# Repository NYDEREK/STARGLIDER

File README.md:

<h1>STARGLIDER MainBoard rev1 - Datasheet</h1>

<h2>Main Board Features</h2>

<ul>
  <li>STM32G474RET6 microcontroller in LQFP64 package</li>
  <li>RGB LED diode</li>
  <li>JST SH SM0XB SSR TB connectors</li>
  <li>MIPI10 - STDC14 programmer connector</li>
  <li>Tag connector programmer footprint</li>
  <li>Micro SD card slot</li>
  <li>Buzzer</li>
  <li>BME280 Temperature, Humidity &amp; Pressure sensor</li>
  <li>LSM6DS3 Accelerometer &amp; Gyroscope IMU module</li>
  <li>USB 2.0 connector</li>
</ul>

<h2>Description</h2>
<p>
Main Board is the most important PCB in the STARGLIDER build.  
It controls all other modules, saves data on the micro-SD card, calculates flight data 
such as attitude, roll, pitch, and yaw, and measures Temperature, Humidity, and Pressure.  
Thanks to the built-in “Cordic” it is able to easily calculate flight path &amp; Kalman filter.
</p>

<h2>Main Board Pinout</h2>

<p>
The Main Board provides 6 different connectors for GPIO, ADC, PWM, Communication, and one connector for Power.  
Input voltage range: <strong>5 – 9 V</strong>.  
Current consumption without external peripherals: <strong>&lt; 1A</strong>.  
Logic pin voltage should not exceed <strong>3.3V</strong>.  
</p>
<p>
Board capabilities include Low-power UART to LSM6DS3 IMU (U7).  
More information is available in the schematic provided in the project files.
</p>

<h2>Programming</h2>

<p>Main Board can be programmed by ST-Link from STMicroelectronics.</p>
<p>Supported development toolchains:</p>
<ul>
  <li>IAR Systems® – IAR Embedded Workbench®</li>
  <li>Keil® – MDK-ARM</li>
  <li>STMicroelectronics – STM32CubeIDE</li>
</ul>

<h2>Measurements</h2>
<p>Main Board is able to measure:</p>
<ul>
  <li>Accelerations</li>
  <li>Angular velocity</li>
  <li>Temperature</li>
  <li>Humidity</li>
  <li>Pressure</li>
  <li>Voltage</li>
</ul>

<h2>LSM6DS3</h2>

<p>
The LSM6DS3TR-C is a system-in-package featuring a 3D digital accelerometer and a 3D digital gyroscope.  
It performs at 0.90 mA in high-performance mode and enables always-on low-power features.  
</p>
<p>
Acceleration range: ±2/±4/±8/±16 g<br>
Angular rate range: ±125/±250/±500/±1000/±2000 dps
</p>

<h2>BME280</h2>

<p>
The BME280 is a combined digital humidity, pressure, and temperature sensor.  
It provides fast response time, high accuracy over a wide temperature range, and optimized low-noise temperature sensing.  
</p>
<p>
Pressure sensor: absolute barometric, high accuracy, lower noise than BMP180.<br>
Temperature output: used for compensation of pressure &amp; humidity, also for ambient temperature estimation.
</p>

<h2>Analog to Digital Converter (ADC)</h2>
<p>The STM32G474RET6 includes 5 successive approximation ADCs with:</p>
<ul>
  <li>12-bit native resolution, built-in calibration</li>
  <li>Up to 4 Msps conversion rate (25 ns sampling time)</li>
  <li>Up to 6.66 Msps at 6-bit resolution</li>
</ul>
<p>
The MCU performance allows the Main Board to measure voltages in the 0 – 3.3 V range with high resolution and speed.
</p>

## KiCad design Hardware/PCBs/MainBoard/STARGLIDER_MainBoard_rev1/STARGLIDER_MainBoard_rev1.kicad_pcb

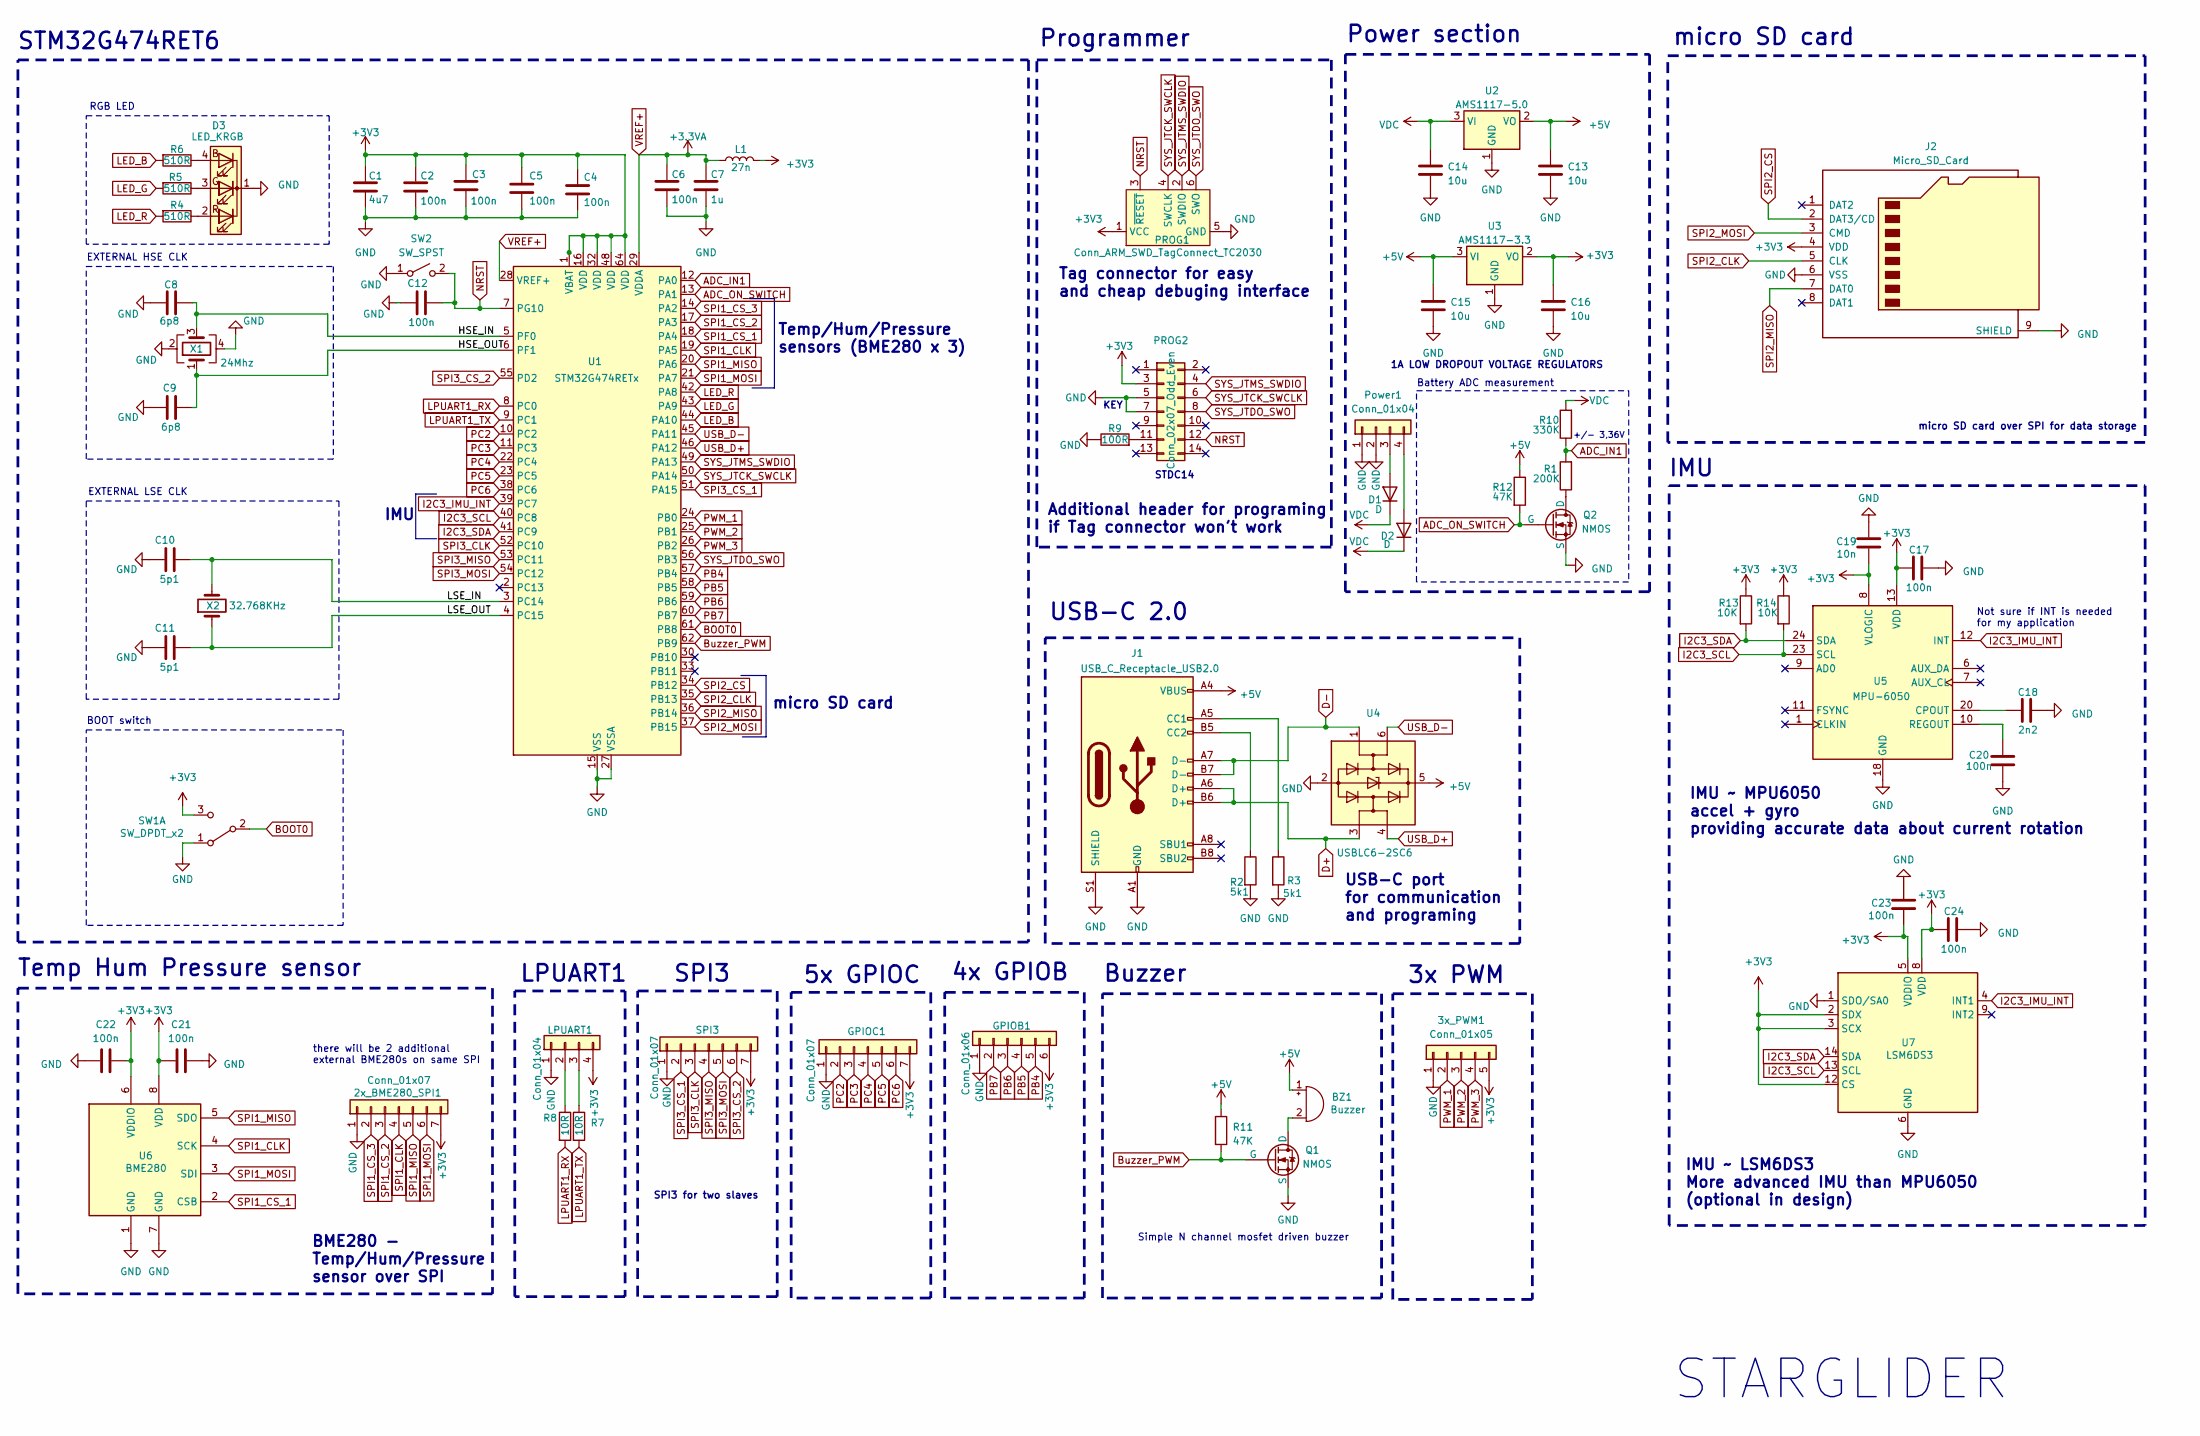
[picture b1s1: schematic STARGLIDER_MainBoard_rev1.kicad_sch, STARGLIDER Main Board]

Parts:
2x_BME280_SPI1: Conn_01x07; JST_SH_SM07B-SRSS-TB_1x07-1MP_P1.00mm_Horizontal
3x_PWM1: Conn_01x05; JST_SH_SM05B-SRSS-TB_1x05-1MP_P1.00mm_Horizontal
BZ1: Buzzer; MagneticBuzzer_PUI_AT-0927-TT-6-R
C1: 4u7; C_0603_1608Metric
C2, C3, C4, C5, C6, C12, C17, C20, C21, C22, C23, C24: 100n; C_0603_1608Metric
C7: 1u; C_0603_1608Metric
C8, C9: 6p8; C_0603_1608Metric
C10, C11: 5p1; C_0603_1608Metric
C13, C14, C15, C16: 10u; C_0603_1608Metric
C18: 2n2; C_0603_1608Metric
C19: 10n; C_0603_1608Metric
D1, D2: D; D_SOD-123
D3: LED_KRGB; LED_RGB_5050-6; Part number TC5050RGBF08-3CJH-AF53A
GPIOB1: Conn_01x06; JST_SH_SM06B-SRSS-TB_1x06-1MP_P1.00mm_Horizontal
GPIOC1: Conn_01x07; JST_SH_SM07B-SRSS-TB_1x07-1MP_P1.00mm_Horizontal
J1: USB_C_Receptacle_USB2.0; USB_C_Receptacle_GCT_USB4105-xx-A_16P_TopMnt_Horizontal
J2: Micro_SD_Card; micro_SD_card
L1: 27n; L_0603_1608Metric
LPUART1: Conn_01x04; JST_SH_SM04B-SRSS-TB_1x04-1MP_P1.00mm_Horizontal
PROG1: Conn_ARM_SWD_TagConnect_TC2030; Tag-Connect_TC2030-IDC-FP_2x03_P1.27mm_Vertical
PROG2: Conn_02x07_Odd_Even; PinHeader_2x07_P1.27mm_Vertical_SMD
Power1: Conn_01x04; JST_SH_SM04B-SRSS-TB_1x04-1MP_P1.00mm_Horizontal
Q1, Q2: NMOS; PUOLOP 2N7002-SOT23
R1: 200K; R_0603_1608Metric
R2, R3: 5k1; R_0603_1608Metric
R4, R5, R6: 510R; R_0603_1608Metric
R7, R8: 10R; R_0603_1608Metric
R9: 100R; R_0603_1608Metric
R10: 330K; R_0603_1608Metric
R11, R12: 47K; R_0603_1608Metric
R13, R14: 10K; R_0603_1608Metric
SPI3: Conn_01x07; JST_SH_SM07B-SRSS-TB_1x07-1MP_P1.00mm_Horizontal
SW1: SW_DPDT_x2; SW_SPDT_PCM12
SW2: SW_SPST; SW_SPST_CK_RS282G05A3
U1: STM32G474RETx; LQFP-64_10x10mm_P0.5mm
U2: AMS1117-5.0; SOT-223-3_TabPin2
U3: AMS1117-3.3; SOT-223-3_TabPin2
U4: USBLC6-2SC6; SOT-23-6
U5: MPU-6050; InvenSense_QFN-24_4x4mm_P0.5mm
U6: BME280; Bosch_LGA-8_2.5x2.5mm_P0.65mm_ClockwisePinNumbering
U7: LSM6DS3; LGA-14_3x2.5mm_P0.5mm_LayoutBorder3x4y
X1: 24Mhz; Crystal_SMD_2016-4Pin_2.0x1.6mm
X2: 32.768KHz; Crystal_SMD_3215-2Pin_3.2x1.5mm

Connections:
+3V3: 2x_BME280_SPI1.7, 3x_PWM1.5, C1.1, C2.1, C3.1, C4.1, C5.1, C16.1, C17.2, C19.1, C21.1, C22.2, C23.1, C24.2, GPIOB1.6, GPIOC1.7, J2.4 (VDD), L1.2, LPUART1.4, PROG1.1 (VCC), PROG2.3, R13.1, R14.1, SPI3.7, SW1.3 (C), U1.1 (VBAT), U1.16 (VDD), U1.32 (VDD), U1.48 (VDD), U1.64 (VDD), U3.2 (VO), U5.8 (VLOGIC), U5.13 (VDD), U6.6 (VDDIO), U6.8 (VDD), U7.2 (SDX), U7.3 (SCX), U7.5 (VDDIO), U7.8 (VDD), U7.12 (CS); also elsewhere on the board
+5V: BZ1.1 (-), C13.1, C15.1, J1.A4 (VBUS), J1.A9 (VBUS), J1.B4 (VBUS), J1.B9 (VBUS), R11.1, R12.1, U2.2 (VO), U3.3 (VI), U4.5 (VBUS)
/HSE_IN: C8.2, U1.5 (PF0), X1.3
/HSE_OUT: C9.2, U1.6 (PF1), X1.1
/LSE_IN: C10.2, U1.3 (PC14), X2.2
/LSE_OUT: C11.2, U1.4 (PC15), X2.1
ADC_IN1: R1.2, R10.1, U1.12 (PA0)
ADC_ON_SWITCH: Q2.2 (G), R12.2, U1.13 (PA1)
BOOT0: SW1.2 (B), U1.61 (PB8); also elsewhere on the board
Buzzer_PWM: Q1.2 (G), R11.2, U1.62 (PB9)
D+: J1.A6 (D+), J1.B6 (D+), U4.3 (I/O2)
D-: J1.A7 (D-), J1.B7 (D-), U4.1 (I/O1)
GND: 2x_BME280_SPI1.1, 3x_PWM1.1, C1.2, C2.2, C3.2, C4.2, C5.2, C6.2, C7.2, C8.1, C9.1, C10.1, C11.1, C12.1, C13.2, C14.2, C15.2, C16.2, C17.1, C18.1, C19.2, C20.2, C21.2, C22.1, C23.2, C24.1, D3.1 (K), GPIOB1.1, GPIOC1.1, J1.A1 (GND), J1.A12 (GND), J1.B1 (GND), J1.B12 (GND), J1.S1 (SHIELD), J2.6 (VSS), J2.9 (SHIELD), LPUART1.1, PROG1.5 (GND), PROG2.5, PROG2.7, Power1.1, Power1.2, Q1.3 (S), Q2.3 (S), R2.2, R3.2, R9.1, SPI3.1, SW1.1 (A), SW2.1 (A), U1.15 (VSS), U1.27 (VSSA), U1.31 (VSS), U1.47 (VSS), U1.63 (VSS), U2.1 (GND), U3.1 (GND), U4.2 (GND), U5.18 (GND), U6.1 (GND), U6.7 (GND), U7.1 (SDO/SA0), U7.6 (GND), U7.7 (GND), X1.2, X1.4; also elsewhere on the board
I2C3_IMU_INT: U1.39 (PC7), U5.12 (INT), U7.4 (INT1)
I2C3_SCL: R14.2, U1.40 (PC8), U5.23 (SCL), U7.13 (SCL)
I2C3_SDA: R13.2, U1.41 (PC9), U5.24 (SDA), U7.14 (SDA)
LED_B: R6.2, U1.44 (PA10)
LED_G: R5.2, U1.43 (PA9)
LED_R: R4.2, U1.42 (PA8)
LPUART1_RX: R8.2, U1.8 (PC0)
LPUART1_TX: R7.2, U1.9 (PC1)
NRST: C12.2, PROG1.3 (~RESET), PROG2.12, SW2.2 (B), U1.7 (PG10); also elsewhere on the board
unnamed: BZ1.2 (+), Q1.1 (D)
unnamed: D1.2 (A), Power1.3
unnamed: D2.2 (A), Power1.4
unnamed: D3.4 (BA), R6.1
unnamed: D3.3 (GA), R5.1
unnamed: D3.2 (RA), R4.1
unnamed: J1.A5 (CC1), R3.1
unnamed: J1.B5 (CC2), R2.1
unnamed: LPUART1.2, R8.1
unnamed: LPUART1.3, R7.1
unnamed 32: PROG2.11, R9.2; also elsewhere on the board
unnamed: Q2.1 (D), R1.1
unnamed: C18.2, U5.20 (CPOUT)
unnamed: C20.1, U5.10 (REGOUT)
PB4: GPIOB1.5, U1.57 (PB4)
PB5: GPIOB1.4, U1.58 (PB5)
PB6: GPIOB1.3, U1.59 (PB6)
PB7: GPIOB1.2, U1.60 (PB7)
PC2: GPIOC1.2, U1.10 (PC2)
PC3: GPIOC1.3, U1.11 (PC3)
PC4: GPIOC1.4, U1.22 (PC4)
PC5: GPIOC1.5, U1.23 (PC5)
PC6: GPIOC1.6, U1.38 (PC6)
PWM_1: 3x_PWM1.2, U1.24 (PB0)
PWM_2: 3x_PWM1.3, U1.25 (PB1)
PWM_3: 3x_PWM1.4, U1.26 (PB2)
SPI1_CLK: 2x_BME280_SPI1.4, U1.19 (PA5), U6.4 (SCK)
SPI1_CS_1: U1.18 (PA4), U6.2 (CSB)
SPI1_CS_2: 2x_BME280_SPI1.3, U1.17 (PA3)
SPI1_CS_3: 2x_BME280_SPI1.2, U1.14 (PA2)
SPI1_MISO: 2x_BME280_SPI1.5, U1.20 (PA6), U6.5 (SDO)
SPI1_MOSI: 2x_BME280_SPI1.6, U1.21 (PA7), U6.3 (SDI)
SPI2_CLK: J2.5 (CLK), U1.35 (PB13)
SPI2_CS: J2.2 (DAT3/CD), U1.34 (PB12)
SPI2_MISO: J2.7 (DAT0), U1.36 (PB14)
SPI2_MOSI: J2.3 (CMD), U1.37 (PB15)
SPI3_CLK: SPI3.3, U1.52 (PC10)
SPI3_CS_1: SPI3.2, U1.51 (PA15)
SPI3_CS_2: SPI3.6, U1.55 (PD2)
SPI3_MISO: SPI3.4, U1.53 (PC11)
SPI3_MOSI: SPI3.5, U1.54 (PC12)
SYS_JTCK_SWCLK: PROG1.4 (SWCLK), PROG2.6, U1.50 (PA14); also elsewhere on the board
SYS_JTDO_SWO: PROG1.6 (SWO), PROG2.8, U1.56 (PB3); also elsewhere on the board
SYS_JTMS_SWDIO: PROG1.2 (SWDIO), PROG2.4, U1.49 (PA13); also elsewhere on the board
USB_D+: U1.46 (PA12), U4.4 (I/O2)
USB_D-: U1.45 (PA11), U4.6 (I/O1)
VDC: C14.1, D1.1 (K), D2.1 (K), R10.2, U2.3 (VI)
VREF+: C6.1, C7.1, L1.1, U1.28 (VREF+), U1.29 (VDDA)

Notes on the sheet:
BME280 - Temp/Hum/Pressure sensor over SPI
KEY
Programmer
IMU
STM32G474RET6
micro SD card
USB-C 2.0
SPI3 for two slaves
3x PWM
Tag connector for easy and cheap debuging interface
Additional header for programing if Tag connector won't work
IMU ~ MPU6050 accel + gyro providing accurate data about current rotation
Not sure if INT is needed for my application
SPI3
LPUART1
micro SD card over SPI for data storage
+/- 3,36V
BOOT switch
STARGLIDER
4x GPIOB
EXTERNAL HSE CLK
RGB LED
there will be 2 additional external BME280s on same SPI
IMU ~ LSM6DS3 More advanced IMU than MPU6050 (optional in design)
Simple N channel mosfet driven buzzer
Temp/Hum/Pressure sensors (BME280 x 3)
5x GPIOC
Buzzer
Power section
USB-C port for communication and programing
1A LOW DROPOUT VOLTAGE REGULATORS
Battery ADC measurement
EXTERNAL LSE CLK
Temp Hum Pressure sensor
STDC14

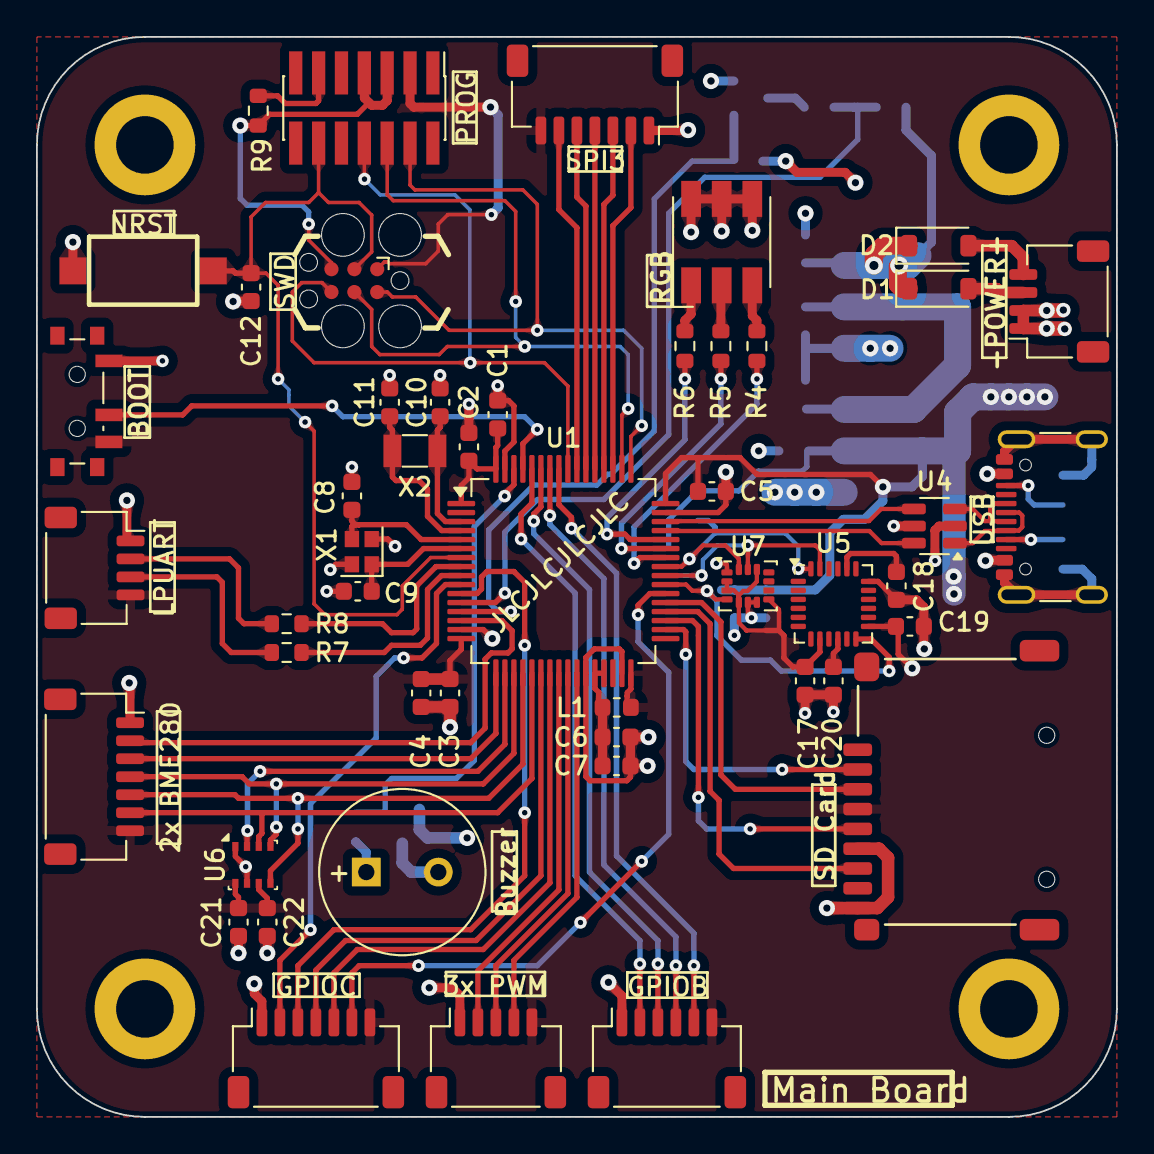
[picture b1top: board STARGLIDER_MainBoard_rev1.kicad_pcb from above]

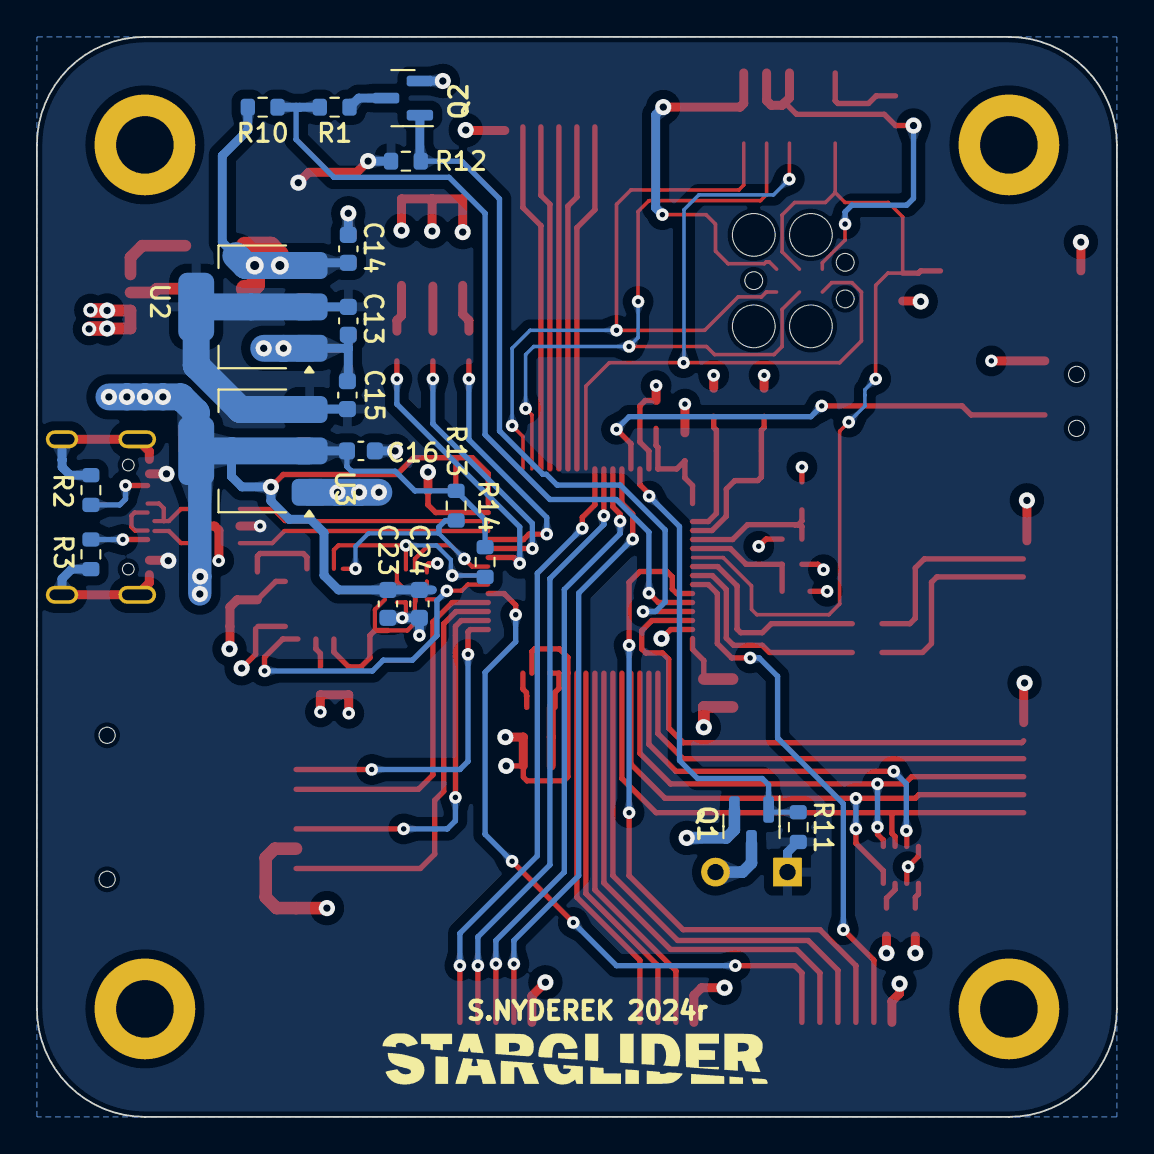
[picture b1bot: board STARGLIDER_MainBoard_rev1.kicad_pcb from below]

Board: 4 copper layers, 60.0 x 60.0 mm, 67 parts (18 on the bottom side), 70 nets.

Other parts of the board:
BOOT: SW_DPDT_x2; SW_SPDT_PCM12
PROG: Conn_02x07_Odd_Even; PinHeader_2x07_P1.27mm_Vertical_SMD

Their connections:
+3V3: BOOT.3 (C), PROG.3; also elsewhere on the board
BOOT0: BOOT.2 (B); also elsewhere on the board
GND: BOOT.1 (A), PROG.5, PROG.7; also elsewhere on the board
NRST: PROG.12; also elsewhere on the board
unnamed 32: PROG.11; also elsewhere on the board
SYS_JTCK_SWCLK: PROG.6; also elsewhere on the board
SYS_JTDO_SWO: PROG.8; also elsewhere on the board
SYS_JTMS_SWDIO: PROG.4; also elsewhere on the board

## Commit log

2024-08-18 V0.0
2024-08-18 V0.1
2024-09-02 Main Board rev1 done
